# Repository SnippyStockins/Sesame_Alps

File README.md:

# Sesame_Alps

### Partslist
 |Count|Part|
 |-|-|

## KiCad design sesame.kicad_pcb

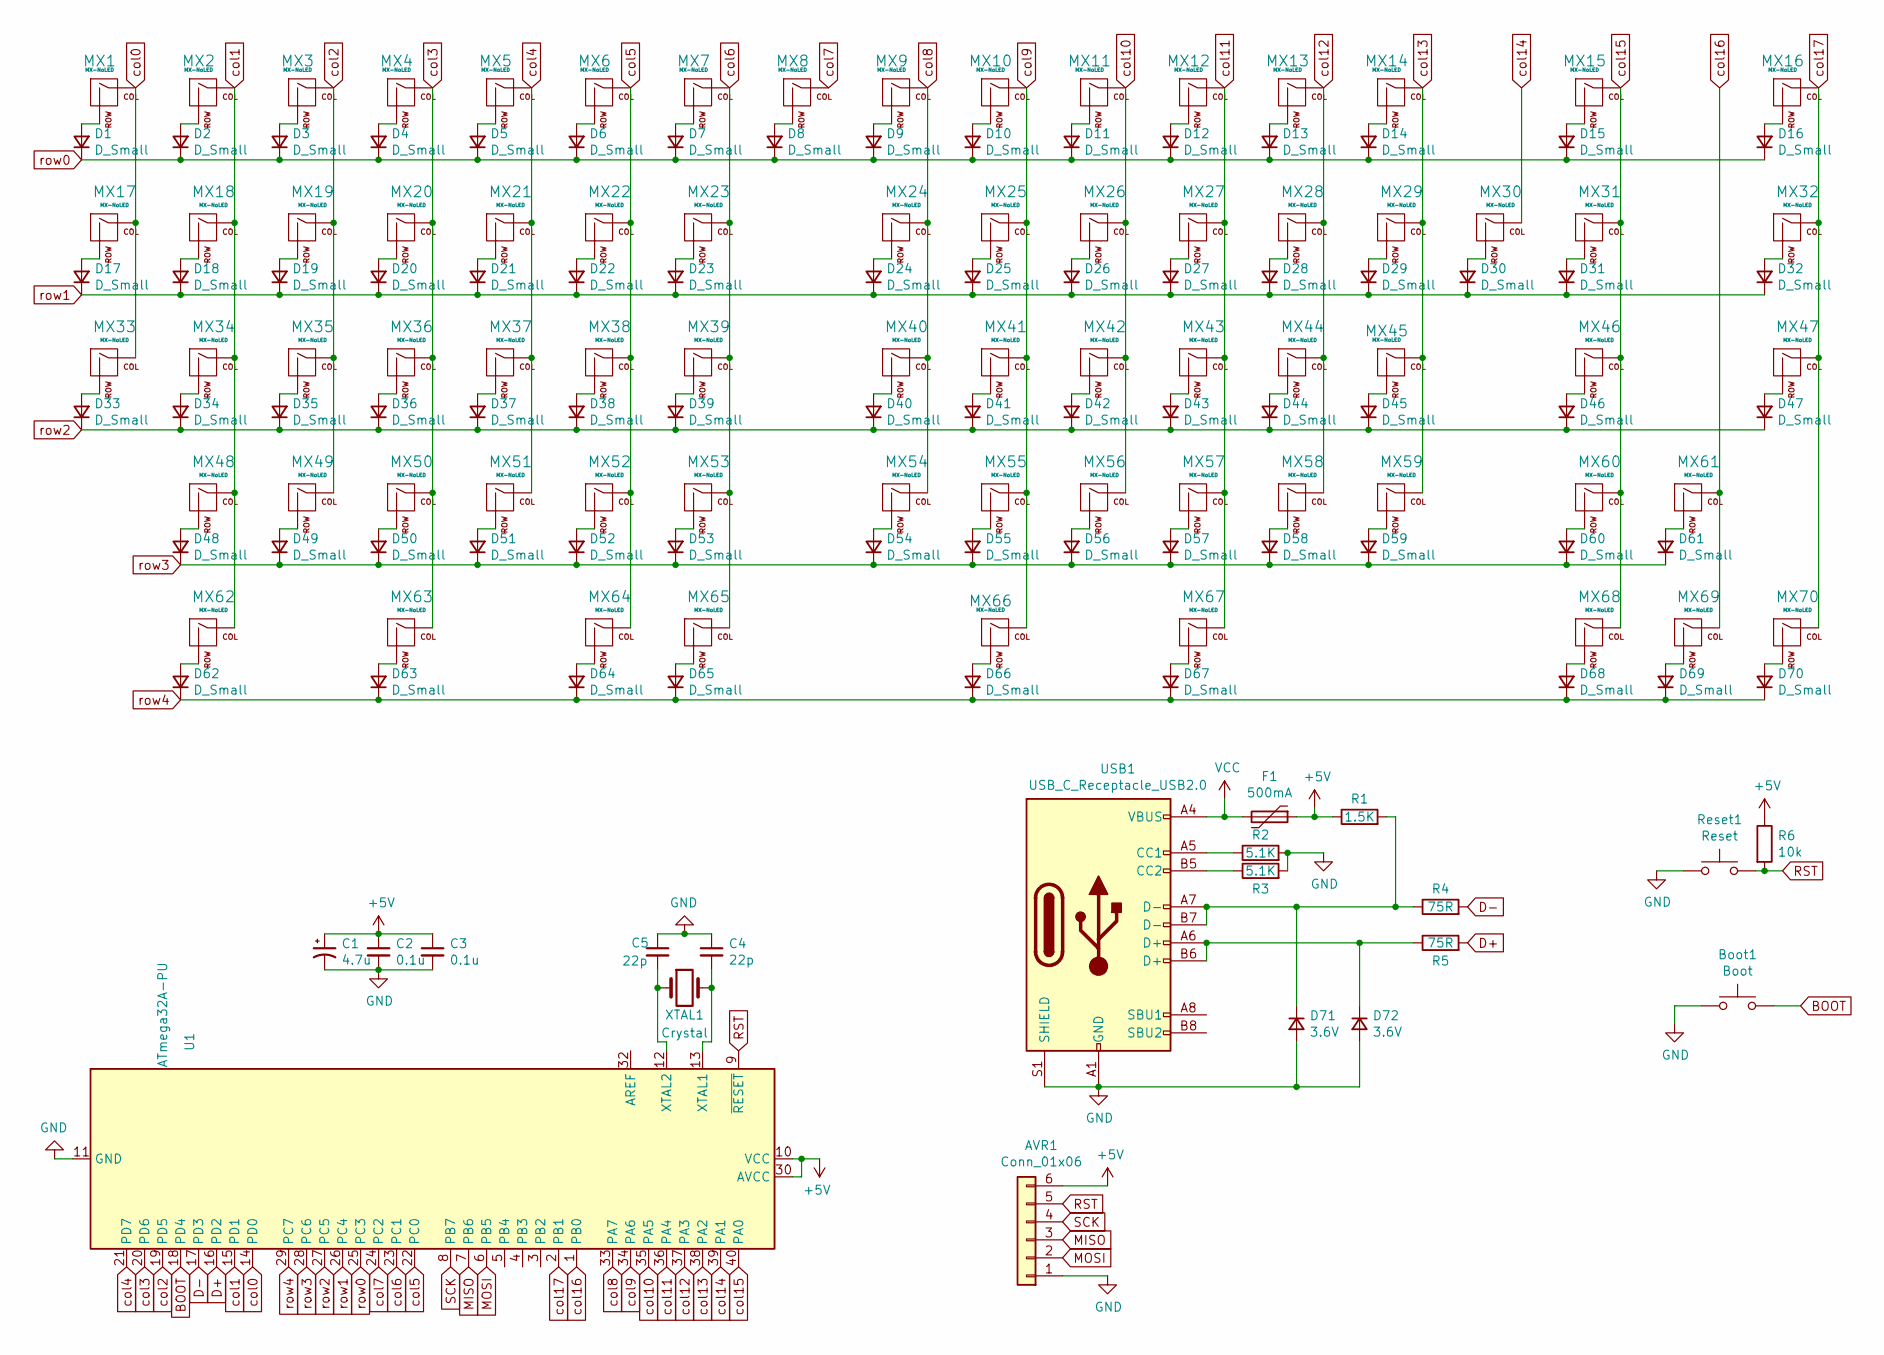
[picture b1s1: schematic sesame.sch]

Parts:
AVR1: Conn_01x06; PinHeader_1x06_P2.54mm_Vertical
Boot1: Boot; SW_PUSH_6mm
C1: 4.7u; CP_Radial_D4.0mm_P1.50mm
C2, C3: 0.1u; C_Disc_D4.3mm_W1.9mm_P5.00mm
C4, C5: 22p; C_Disc_D3.0mm_W1.6mm_P2.50mm
D1, D2, D3, D4, D5, D6, D7, D8, D9, D10, D11, D12, D13, D14, D15, D16, D17, D18, D19, D20, D21, D22, D23, D24, D25, D26, D27, D28, D29, D30, D31, D32, D33, D34, D35, D36, D37, D38, D39, D40, D41, D42, D43, D44, D45, D46, D47, D48, D49, D50, D51, D52, D53, D54, D55, D56, D57, D58, D59, D60, D61, D62, D63, D64, D65, D66, D67, D68, D69, D70: D_Small; D_DO-35_SOD27_P7.62mm_Horizontal
D71, D72: 3.6V; D_DO-35_SOD27_P7.62mm_Horizontal
F1: 500mA; Fuse_Littelfuse_395Series
MX1, MX2, MX3, MX4, MX5, MX6, MX7, MX8, MX9, MX10, MX11, MX12, MX13, MX14, MX16, MX17, MX19, MX20, MX21, MX22, MX23, MX24, MX25, MX26, MX27, MX28, MX29, MX30, MX32, MX33, MX35, MX36, MX37, MX38, MX39, MX40, MX41, MX42, MX43, MX44, MX45, MX47, MX49, MX50, MX51, MX52, MX53, MX54, MX55, MX56, MX57, MX58, MX59, MX61, MX68, MX69, MX70: MX-NoLED; MX-1U-NoLED
MX15: MX-NoLED; MX-2U-NoLED
MX18, MX31: MX-NoLED; MX-1.5U-NoLED
MX34, MX60: MX-NoLED; MX-1.75U-NoLED
MX46, MX48: MX-NoLED; MX-2.25U-NoLED
MX62, MX63, MX65, MX67: MX-NoLED; MX-1.25U-NoLED
MX64: MX-NoLED; MX-2U-ReversedStabilizers-NoLED
MX66: MX-NoLED; MX-2.75U-ReversedStabilizers-NoLED
R1: 1.5K; R_Axial_DIN0204_L3.6mm_D1.6mm_P7.62mm_Horizontal
R2, R3: 5.1K; R_Axial_DIN0204_L3.6mm_D1.6mm_P7.62mm_Horizontal
R4, R5: 75R; R_Axial_DIN0204_L3.6mm_D1.6mm_P7.62mm_Horizontal
R6: 10k; R_Axial_DIN0204_L3.6mm_D1.6mm_P7.62mm_Horizontal
Reset1: Reset; SW_PUSH_6mm
U1: ATmega32A-PU; DIP-40_W15.24mm
USB1: USB_C_Receptacle_USB2.0; USB_C_Receptacle_GCT_USB4085
XTAL1: Crystal; Crystal_HC49-4H_Vertical

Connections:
+5V: AVR1.6, C1.1, C2.1, C3.1, F1.1, R1.1, R6.1, U1.10 (VCC), U1.30 (AVCC)
BOOT: Boot1.2, U1.18 (PD4)
D+: R5.2, U1.16 (PD2)
D-: R4.2, U1.17 (PD3)
GND: AVR1.1, Boot1.1, C1.2, C2.2, C3.2, C4.1, C5.1, D71.2 (A), D72.2 (A), R2.2, R3.2, Reset1.1, U1.11 (GND), U1.31 (GND), USB1.A1 (GND), USB1.A12 (GND), USB1.B1 (GND), USB1.B12 (GND), USB1.S1 (SHIELD)
MISO: AVR1.3, U1.7 (PB6)
MOSI: AVR1.2, U1.6 (PB5)
unnamed: C4.2, U1.13 (XTAL1), XTAL1.2
unnamed: C5.2, U1.12 (XTAL2), XTAL1.1
unnamed: D1.2 (A), MX1.2 (ROW)
unnamed: D2.2 (A), MX2.2 (ROW)
unnamed: D3.2 (A), MX3.2 (ROW)
unnamed: D4.2 (A), MX4.2 (ROW)
unnamed: D5.2 (A), MX5.2 (ROW)
unnamed: D6.2 (A), MX6.2 (ROW)
unnamed: D7.2 (A), MX7.2 (ROW)
unnamed: D8.2 (A), MX8.2 (ROW)
unnamed: D9.2 (A), MX9.2 (ROW)
unnamed: D10.2 (A), MX10.2 (ROW)
unnamed: D11.2 (A), MX11.2 (ROW)
unnamed: D12.2 (A), MX12.2 (ROW)
unnamed: D13.2 (A), MX13.2 (ROW)
unnamed: D14.2 (A), MX14.2 (ROW)
unnamed: D15.2 (A), MX15.2 (ROW)
unnamed: D16.2 (A), MX16.2 (ROW)
unnamed: D17.2 (A), MX17.2 (ROW)
unnamed: D18.2 (A), MX18.2 (ROW)
unnamed: D19.2 (A), MX19.2 (ROW)
unnamed: D20.2 (A), MX20.2 (ROW)
unnamed: D21.2 (A), MX21.2 (ROW)
unnamed: D22.2 (A), MX22.2 (ROW)
unnamed: D23.2 (A), MX23.2 (ROW)
unnamed: D24.2 (A), MX24.2 (ROW)
unnamed: D25.2 (A), MX25.2 (ROW)
unnamed: D26.2 (A), MX26.2 (ROW)
unnamed: D27.2 (A), MX27.2 (ROW)
unnamed: D28.2 (A), MX28.2 (ROW)
unnamed: D29.2 (A), MX29.2 (ROW)
unnamed: D30.2 (A), MX30.2 (ROW)
unnamed: D31.2 (A), MX31.2 (ROW)
unnamed: D32.2 (A), MX32.2 (ROW)
unnamed: D33.2 (A), MX33.2 (ROW)
unnamed: D34.2 (A), MX34.2 (ROW)
unnamed: D35.2 (A), MX35.2 (ROW)
unnamed: D36.2 (A), MX36.2 (ROW)
unnamed: D37.2 (A), MX37.2 (ROW)
unnamed: D38.2 (A), MX38.2 (ROW)
unnamed: D39.2 (A), MX39.2 (ROW)
unnamed: D40.2 (A), MX40.2 (ROW)
unnamed: D41.2 (A), MX41.2 (ROW)
unnamed: D42.2 (A), MX42.2 (ROW)
unnamed: D43.2 (A), MX43.2 (ROW)
unnamed: D44.2 (A), MX44.2 (ROW)
unnamed: D45.2 (A), MX45.2 (ROW)
unnamed: D46.2 (A), MX46.2 (ROW)
unnamed: D47.2 (A), MX47.2 (ROW)
unnamed: D48.2 (A), MX48.2 (ROW)
unnamed: D49.2 (A), MX49.2 (ROW)
unnamed: D50.2 (A), MX50.2 (ROW)
unnamed: D51.2 (A), MX51.2 (ROW)
unnamed: D52.2 (A), MX52.2 (ROW)
unnamed: D53.2 (A), MX53.2 (ROW)
unnamed: D54.2 (A), MX54.2 (ROW)
unnamed: D55.2 (A), MX55.2 (ROW)
unnamed: D56.2 (A), MX56.2 (ROW)
unnamed: D57.2 (A), MX57.2 (ROW)
unnamed: D58.2 (A), MX58.2 (ROW)
unnamed: D59.2 (A), MX59.2 (ROW)
unnamed: D60.2 (A), MX60.2 (ROW)
unnamed: D61.2 (A), MX61.2 (ROW)
unnamed: D62.2 (A), MX62.2 (ROW)
unnamed: D63.2 (A), MX63.2 (ROW)
unnamed: D64.2 (A), MX64.2 (ROW)
unnamed: D65.2 (A), MX65.2 (ROW)
unnamed: D66.2 (A), MX66.2 (ROW)
unnamed: D67.2 (A), MX67.2 (ROW)
unnamed: D68.2 (A), MX68.2 (ROW)
unnamed: D69.2 (A), MX69.2 (ROW)
unnamed: D70.2 (A), MX70.2 (ROW)
unnamed: D71.1 (K), R1.2, R4.1, USB1.A7 (D-), USB1.B7 (D-)
unnamed: D72.1 (K), R5.1, USB1.A6 (D+), USB1.B6 (D+)
unnamed: R2.1, USB1.A5 (CC1)
unnamed: R3.1, USB1.B5 (CC2)
RST: AVR1.5, R6.2, Reset1.2, U1.9 (~RESET)
SCK: AVR1.4, U1.8 (PB7)
VCC: F1.2, USB1.A4 (VBUS), USB1.A9 (VBUS), USB1.B4 (VBUS), USB1.B9 (VBUS)
col0: MX1.1 (COL), MX17.1 (COL), MX33.1 (COL), U1.14 (PD0)
col1: MX2.1 (COL), MX18.1 (COL), MX34.1 (COL), MX48.1 (COL), MX62.1 (COL), U1.15 (PD1)
col2: MX3.1 (COL), MX19.1 (COL), MX35.1 (COL), MX49.1 (COL), U1.19 (PD5)
col3: MX4.1 (COL), MX20.1 (COL), MX36.1 (COL), MX50.1 (COL), MX63.1 (COL), U1.20 (PD6)
col4: MX5.1 (COL), MX21.1 (COL), MX37.1 (COL), MX51.1 (COL), U1.21 (PD7)
col5: MX6.1 (COL), MX22.1 (COL), MX38.1 (COL), MX52.1 (COL), MX64.1 (COL), U1.22 (PC0)
col6: MX7.1 (COL), MX23.1 (COL), MX39.1 (COL), MX53.1 (COL), MX65.1 (COL), U1.23 (PC1)
col7: MX8.1 (COL), U1.24 (PC2)
col8: MX9.1 (COL), MX24.1 (COL), MX40.1 (COL), MX54.1 (COL), U1.33 (PA7)
col9: MX10.1 (COL), MX25.1 (COL), MX41.1 (COL), MX55.1 (COL), MX66.1 (COL), U1.34 (PA6)
col10: MX11.1 (COL), MX26.1 (COL), MX42.1 (COL), MX56.1 (COL), U1.35 (PA5)
col11: MX12.1 (COL), MX27.1 (COL), MX43.1 (COL), MX57.1 (COL), MX67.1 (COL), U1.36 (PA4)
col12: MX13.1 (COL), MX28.1 (COL), MX44.1 (COL), MX58.1 (COL), U1.37 (PA3)
col13: MX14.1 (COL), MX29.1 (COL), MX45.1 (COL), MX59.1 (COL), U1.38 (PA2)
col14: MX30.1 (COL), U1.39 (PA1)
col15: MX15.1 (COL), MX31.1 (COL), MX46.1 (COL), MX60.1 (COL), MX68.1 (COL), U1.40 (PA0)
col16: MX61.1 (COL), MX69.1 (COL), U1.1 (PB0)
col17: MX16.1 (COL), MX32.1 (COL), MX47.1 (COL), MX70.1 (COL), U1.2 (PB1)
row0: D1.1 (K), D2.1 (K), D3.1 (K), D4.1 (K), D5.1 (K), D6.1 (K), D7.1 (K), D8.1 (K), D9.1 (K), D10.1 (K), D11.1 (K), D12.1 (K), D13.1 (K), D14.1 (K), D15.1 (K), D16.1 (K), U1.25 (PC3)
row1: D17.1 (K), D18.1 (K), D19.1 (K), D20.1 (K), D21.1 (K), D22.1 (K), D23.1 (K), D24.1 (K), D25.1 (K), D26.1 (K), D27.1 (K), D28.1 (K), D29.1 (K), D30.1 (K), D31.1 (K), D32.1 (K), U1.26 (PC4)
row2: D33.1 (K), D34.1 (K), D35.1 (K), D36.1 (K), D37.1 (K), D38.1 (K), D39.1 (K), D40.1 (K), D41.1 (K), D42.1 (K), D43.1 (K), D44.1 (K), D45.1 (K), D46.1 (K), D47.1 (K), U1.27 (PC5)
row3: D48.1 (K), D49.1 (K), D50.1 (K), D51.1 (K), D52.1 (K), D53.1 (K), D54.1 (K), D55.1 (K), D56.1 (K), D57.1 (K), D58.1 (K), D59.1 (K), D60.1 (K), D61.1 (K), U1.28 (PC6)
row4: D62.1 (K), D63.1 (K), D64.1 (K), D65.1 (K), D66.1 (K), D67.1 (K), D68.1 (K), D69.1 (K), D70.1 (K), U1.29 (PC7)

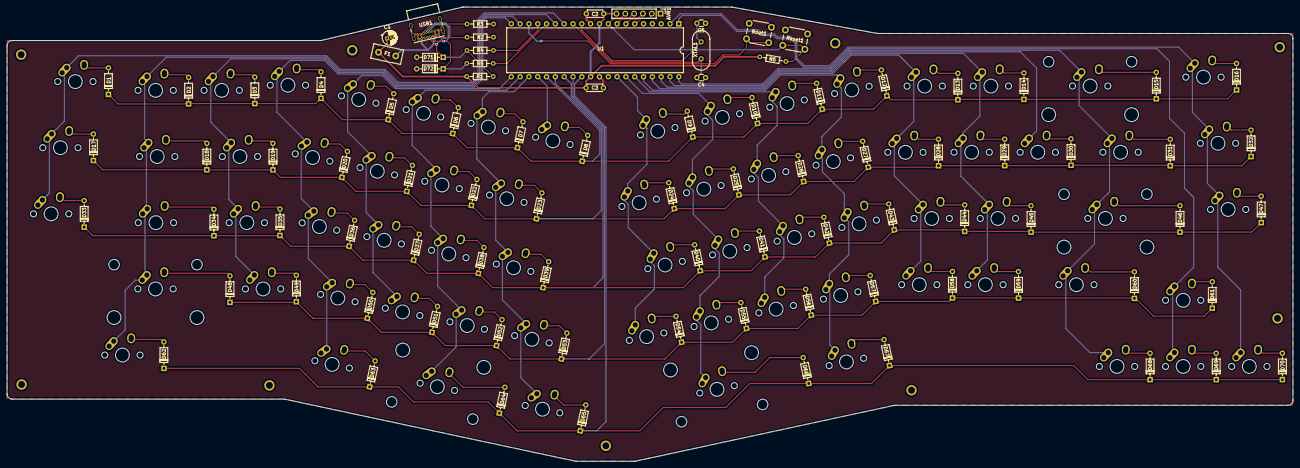
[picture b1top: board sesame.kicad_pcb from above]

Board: 2 copper layers, 370.3 x 130.8 mm, 160 parts (0 on the bottom side), 109 nets.
